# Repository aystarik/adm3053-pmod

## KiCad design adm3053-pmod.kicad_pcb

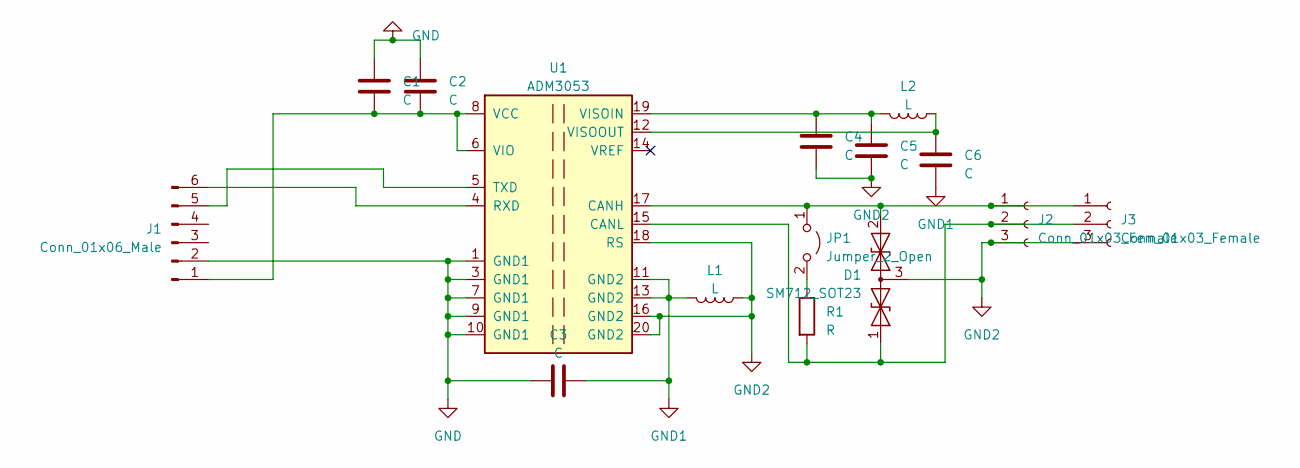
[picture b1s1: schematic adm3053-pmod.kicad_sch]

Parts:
C1, C2, C4, C5, C6: C; C_0603_1608Metric_Pad1.08x0.95mm_HandSolder
C3: C; C_1812_4532Metric_Pad1.57x3.40mm_HandSolder
D1: SM712_SOT23; SOT-23
J1: Conn_01x06_Male; PinHeader_1x06_P2.54mm_Horizontal
J2, J3: Conn_01x03_Female; PinHeader_1x03_P2.54mm_Vertical
JP1: Jumper_2_Open; PinHeader_1x02_P2.54mm_Vertical
L1, L2: L; L_0603_1608Metric_Pad1.05x0.95mm_HandSolder
R1: R; R_0603_1608Metric_Pad0.98x0.95mm_HandSolder
U1: ADM3053; SOIC-20W_7.5x12.8mm_P1.27mm

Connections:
GND: C1.2, C2.2, C3.1, J1.2, U1.1 (GND1), U1.3 (GND1), U1.7 (GND1), U1.9 (GND1), U1.10 (GND1)
GND1: C3.2, C6.1, L1.2, U1.11 (GND2), U1.13 (GND2)
GND2: C4.1, C5.2, D1.3 (common), J2.3, J3.3, L1.1, U1.16 (GND2), U1.18 (RS), U1.20 (GND2)
unnamed: D1.1 (A1), J2.2, J3.2, R1.2, U1.15 (CANL)
unnamed: D1.2 (A2), J2.1, J3.1, JP1.1 (A), U1.17 (CANH)
unnamed: C1.1, C2.1, J1.1, U1.6 (VIO), U1.8 (VCC)
unnamed: J1.5, U1.5 (TXD)
unnamed: J1.6, U1.4 (RXD)
unnamed: JP1.2 (B), R1.1
unnamed: C4.2, C5.1, L2.2, U1.19 (VISOIN)
unnamed: C6.2, L2.1, U1.12 (VISOOUT)

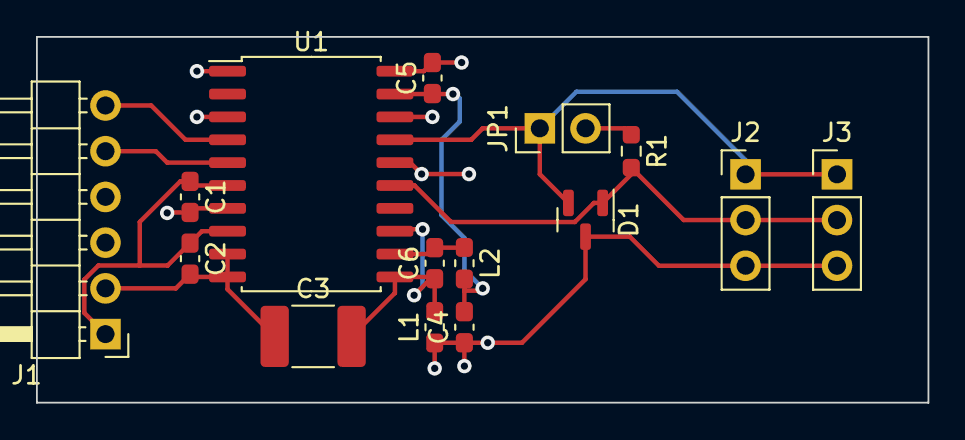
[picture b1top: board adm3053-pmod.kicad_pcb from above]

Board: 2 copper layers, 49.5 x 20.3 mm, 15 parts (0 on the bottom side), 11 nets.

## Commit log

2022-01-06 first
